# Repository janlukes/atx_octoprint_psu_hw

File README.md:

# atx_octoprint_psu_hw
Open source ATX Octoprint PSU for powering 3D printer

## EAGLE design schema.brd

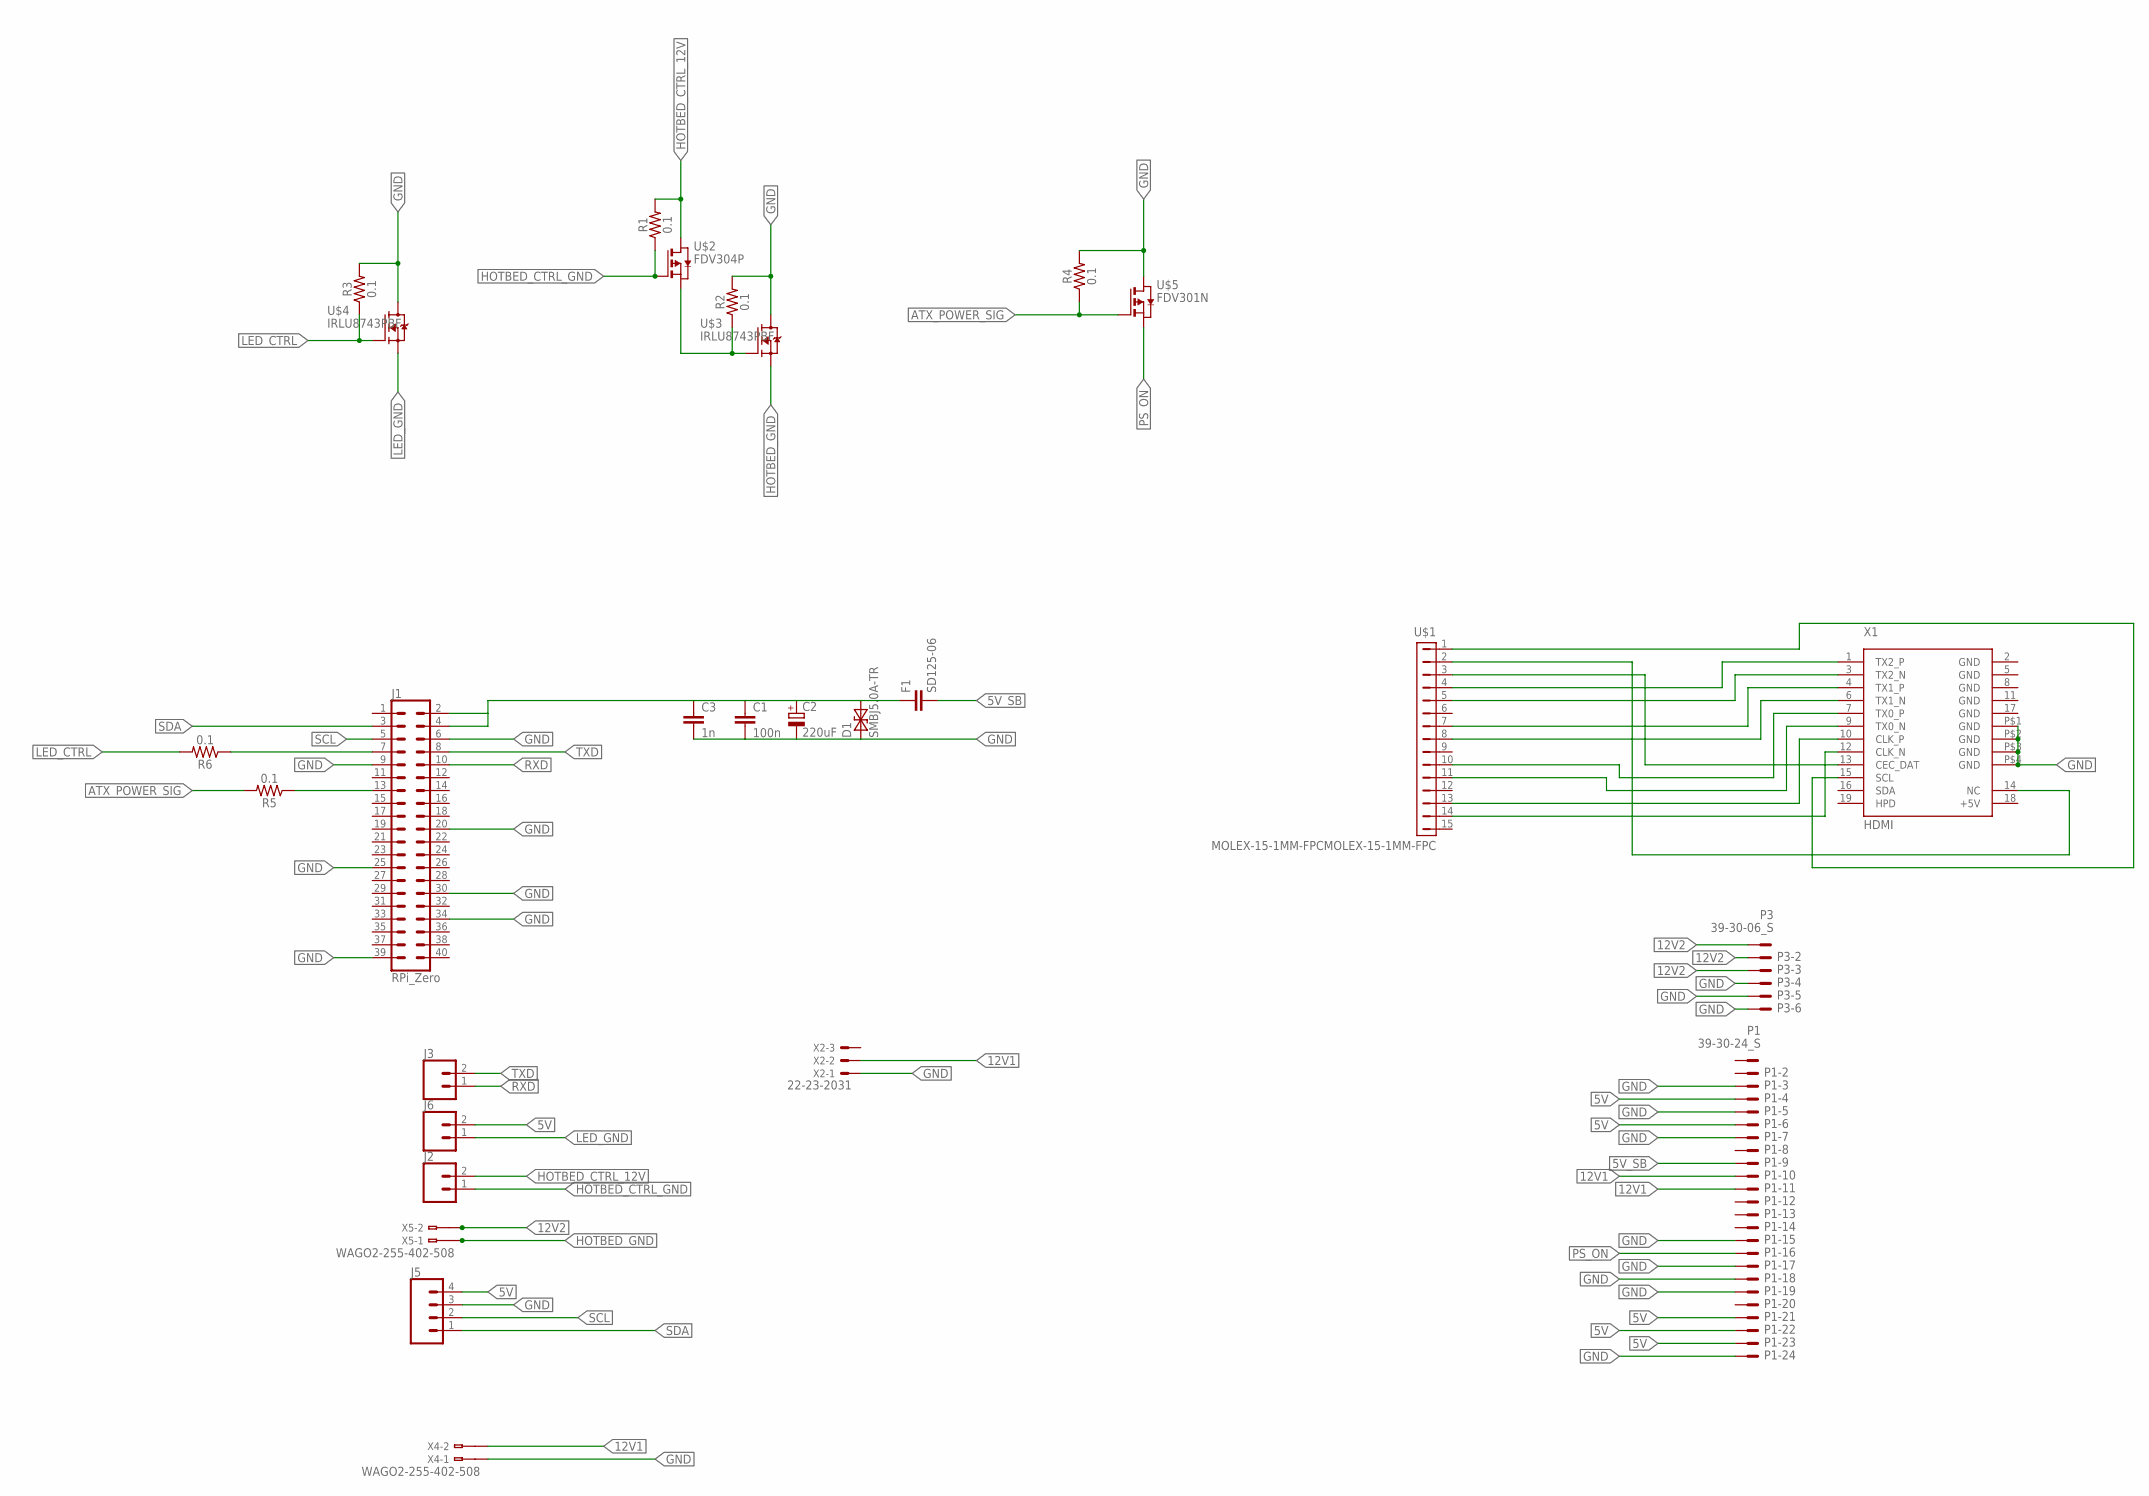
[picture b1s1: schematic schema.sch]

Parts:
C1: 100n; C1206
C2: 220uF; SMC_E
C3: 1n; C1206
D1: SMBJ5.0A-TR; SMB
F1: SD125-06; C1812
J1: RPi_Zero; 2X20
J2, J3: CONN_02; 1X02
J5: CONN_04; 1X04
J6: CONN_025MM; SCREWTERMINAL-5MM-2
P1: 39-30-24_S; 39-30-?24?
P3: 39-30-06_S; 39-30-?06?
R1, R2, R3, R4, R5, R6: 0.1; 1210
U$1: MOLEX-15-1MM-FPCMOLEX-15-1MM-FPC; FH12-15S-1SH
U$2: FDV304P; SOT-23
U$3, U$4: IRLU8743PBF; TO-251AA
U$5: FDV301N; SOT-23
X1: HDMI
X2: 22-23-2031
X4, X5: WAGO2-255-402-508; 255-402-508

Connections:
5V: J5.4, J6.2, P1.4, P1.6, P1.21, P1.22, P1.23
5V_SB: F1.2, P1.9
5V_SB_FUSED: C1.1, C2.+, C3.1, D1.2, F1.1, J1.2, J1.4
12V1: P1.10, P1.11, X2.2, X4.B2 (B1)
12V2: P3.1, P3.2, P3.3, X5.B2 (B1)
ATX_POWER_SIG: R4.1, R5.2, U$5.2 (G)
GND: C1.2, C2.-, C3.2, D1.1, J1.6, J1.9, J1.20, J1.25, J1.30, J1.34, J1.39, J5.3, P1.3, P1.5, P1.7, P1.15, P1.17, P1.18, P1.19, P1.24, P3.4, P3.5, P3.6, R2.2, R3.2, R4.2, U$3.2 (D), U$3.4 (D), U$4.2 (D), U$4.4 (D), U$5.1 (D), X1.P$1 (GND), X1.P$2 (GND), X1.P$3 (GND), X1.P$4 (GND), X2.1, X4.B1
GPIO_7: J1.7, R6.1
GPIO_13: J1.13, R5.1
HOTBED_CTRL_12V: J2.2, R1.2, U$2.1 (D)
HOTBED_CTRL_GND: J2.1, R1.1, U$2.2 (G)
HOTBED_GND: U$3.3 (S), X5.B1
LED_CTRL: R3.1, R6.2, U$4.1 (G)
LED_GND: J6.1, U$4.3 (S)
unnamed: R2.1, U$2.3 (S), U$3.1 (G)
unnamed: U$1.2, X1.14 (NC)
unnamed: U$1.1, X1.15 (SCL)
unnamed: U$1.14, X1.12 (CLK_N)
unnamed: U$1.4, X1.1 (TX2_P)
unnamed: U$1.5, X1.3 (TX2_N)
unnamed: U$1.7, X1.4 (TX1_P)
unnamed: U$1.8, X1.6 (TX1_N)
unnamed: U$1.10, X1.7 (TX0_P)
unnamed: U$1.11, X1.9 (TX0_N)
unnamed: U$1.13, X1.10 (CLK_P)
unnamed: U$1.3, X1.13 (CEC_DAT)
PS_ON: P1.16, U$5.3 (S)
RXD: J1.10, J3.1
SCL: J1.5, J5.2
SDA: J1.3, J5.1
TXD: J1.8, J3.2

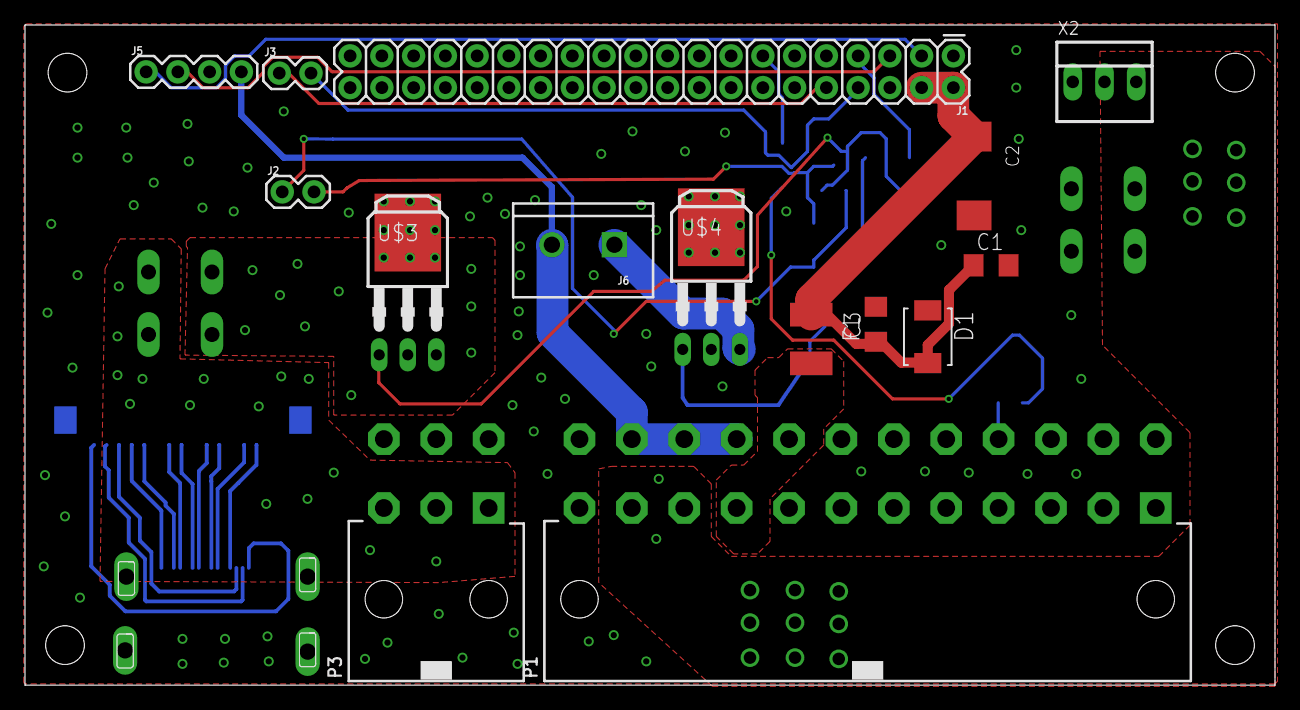
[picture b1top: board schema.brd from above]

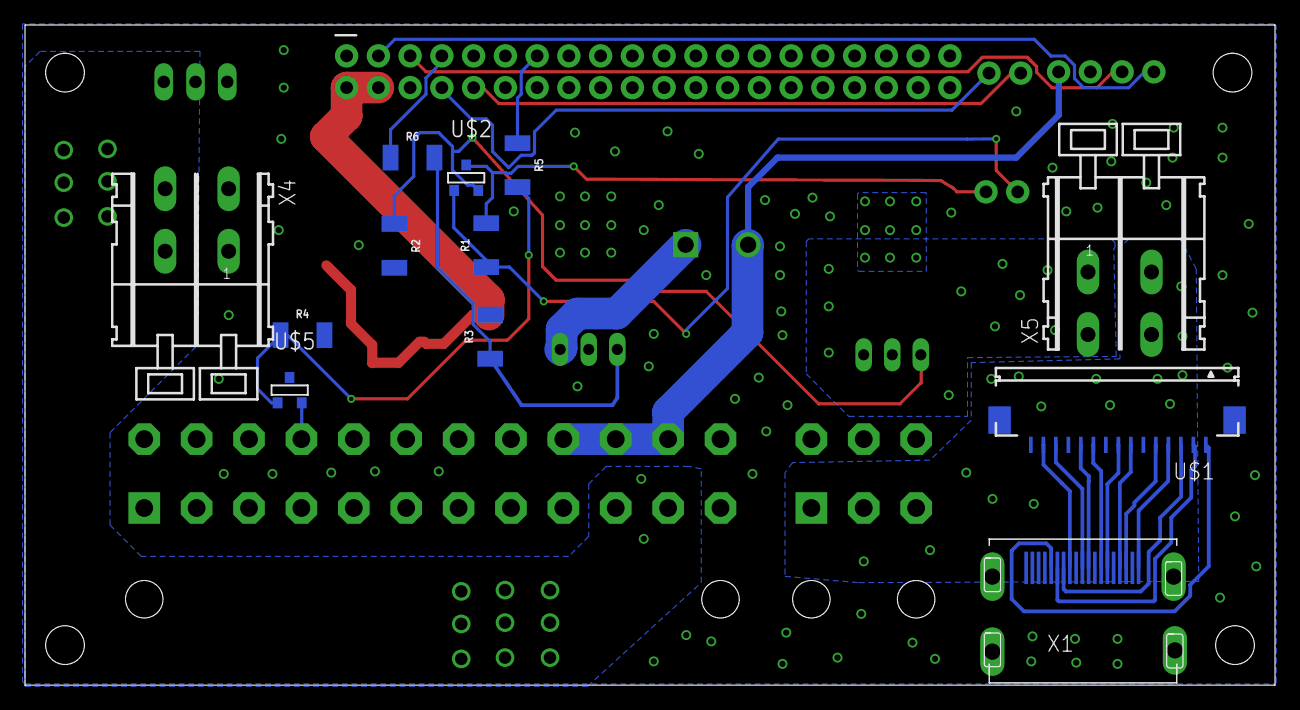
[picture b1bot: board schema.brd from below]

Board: 2 copper layers, 100.0 x 52.8 mm, 27 parts (12 on the bottom side), 31 nets.

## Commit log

2017-10-02 First prototype

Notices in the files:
parts and their libraries:
SparkFun-Connectors: Licensing: Creative Commons ShareAlike 4.0 International - https://creativecommons.org/licenses/by-sa/4.0
con-molex-mini-fit: Copyright (C) 2011, Bob Starr
